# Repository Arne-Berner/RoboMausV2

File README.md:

# Goal
- build a micromouse (from here on out called "rat") from scratch

# Motivation
## The fear of the unknown
I have been working with electronics for a while now, but I never really got into PCB design. I always thought it was too complicated and I would never be able to do it. But I also always wanted to build a micromouse. So I thought, why not combine the two and learn something new in the process.

That being said I also wanted to use my 3D printer more and get rid of that fear that accompanies anything new. Doing this project I feel like I will be able to create electronic devices much more easily in the future. Not only because I learned some tricks on my way, but because I simply have done it before.

## Beginner to Intermediate Rust Project
Let's be honest, coding for embedded systems sound hard. Rust also sounds hard. But weirdly enough, those two things combined are much easier than I thought! I want to provide all the code I used for this project for anyone interested. If you feel like creating electronic devices could be fun, give it a try! Especially the esp32 and rust go really well together. You can [try out Rust on the ESP32 on Wokwi](https://wokwi.com/).

# Parts with their Voltage and Reason I used them

## Placed
### ESP32-s3-mini: 3.3V 
The reason I chose the s3-mini was because it wasn't much more expensive and I was not sure how much processing power will be needed for the project. If I had more time I probably would have chosen an esp32 from the c series. You don't need to use an esp32 at all for a micromouse, but I will need to send the map created by my SLAM-algorithm to my computer via wifi. The STM32 is the MCU that is used for most micromouse.

### USB-C: 5V output
Micro USB tend to break of more easily from PCBs and USB-C has the possibility of using more Volt in later designs, without changing too much.

### AMS1117-3.3: LDO that converts to 3.3V
This seems to be a very common LDO and even though the esp32 is somewhat capable of handling higher voltage than described in the datasheet, I didn't want my project to go up in flames at a bad time.

### L293D (better known as an H-Bridge)
This will let me use my 3.3V from the esp and my 8V from the LiPos to drive my motors. It usually takes one source that ranges from 5V to 36V and another source that will only take 5V. I will see how it works in the project. I could've used an smt h-bridge to minimize the size on the pcb, but running the h-bridge in the wrong manner can destroy it. If that happens (and it will happen) I would like to be able to replace it fast.

### TCS34725 (Color sensor): 2.7V - 3.6V / nom: 3V
I will need to detect the colors of certain places in the labyrinth as an extra task. This seems to be a common and cheap color sensor. It also has a rust library. 

### GY-521 or MPU-6050 (gyroscope sensor): 2.375V - 3.46V
This will help me position orientate my rat. I'm not sure yet, how I will combine this with the input I get from the encoder and what will be used primarily if there is a difference between the two. The mpu-6050 seems to be cheaper but has better specs.

## Not Placed
### SK6812MINI-B-012 (NeoPixel): 5V
This could be used for debugging purposes (and it looks cool), but it needs 5V and that would've drained the LiPos faster than I wanted them to. There is a 3V alternative to the 5V neopixel, but I could not find it on lcsc.

### AMS1117-5.0: LDO that converts to 5V
This would have been necessary if I used the Neopixel above or if the ams1117-3.3 would not be able to handle the lipo voltage.

# Learnings
## How to read a Datasheet instead of "read the datasheet"
When you start in electronics you hear "read the datasheet" a lot. It sounds like bad advice at first, because you probably are asking experienced people about very specific device and datasheets can be hundreds of pages long. Where to start reading up on it? What if there is a feature that you didn't know the name of? Most people rather stop than to "read the datasheet" without knowing where to look for the most important info. 

Later on it feels like "read the datasheet" really was the solution to most problems. But only seemingly so. Experts don't read the full datasheet, even if it is only a few pages long. They won't look at all the data. But they know how to skim the datasheet for the most important info and see if anything is readworthy. But I am no expert and I still need to find answers to my questions. So how to read a datasheet?

There are some basic informations that you most likely want to take a look at:
- volt and ampere (often found as VCC or Vin/Vout info)
- the pinout
- provided example schematics
- (footprints)
With those infos you will have most infos so that your ICs don't burst into flames. It also has the benefit, that most often when looking for those informations you will find other important or odd info that will help you with your project. Be aware that datasheets sometimes contain the data for many variations of IC.

## Copilot and co.
Reading the datasheet might be hard if it is in chinese or if it is hundreds of pages long. Using any LLM to get the gist of it or some pointers where to look for can be very helpfull. But be warned: Especially in electronics halucinations seem to occur very often. They should only be used, if you check the data afterwards. The pinout is very often wrong, the current and voltage vary from the real parts and you can't use it for example schematics. But it will give you words to look for in the datasheet that might be important. 

"What should I be aware of with part XY" or "What could go wrong with wiring X to Y" are the most helpfull prompts.

## Kicad
### Schematics
I like to start with everything at once and see everything come together at the end. But who would have thought that this is neither good in programming, nor in electronics? 

The next project I would definitely draw the schematics for only one or two parts and then check if everything is alright. Do some adjustments, check if everything is alright, put it in the pcb. Rinse and repeat. That way I wouldn't have had to redo big portions of the project and I would have been way faster. Not only that, but I would have some starting point when placing the footprints on the pcb.

Another trick I learned from a friend of mine named "MAG" is to take really good care of a global library and push it to github or any cloud provider. That way you can use it on any machine available to you and using github you could help other people by taking care of that library.

### Libraries and imports
Since I knew I wanted to get the pcb on jlcpcb I mainly used [this website](https://dougy83.github.io/jlcparts/#/) to find the right part. This is a fork of [this repository](https://github.com/yaqwsx/jlcparts) and should be part of that repository soon. It often makes sense to focus on one shop for electronic parts, since shipping and handling fees will stack up fast with different shops. I used [Easyeda cli Plugin](https://github.com/uPesy/easyeda2kicad.py) to get the libraries from EasyEda, since I figured they would fit the parts used by jlc the best.
If I were to start again I would probably use [this Import Plugin](https://github.com/Steffen-W/Import-LIB-KiCad-Plugin#use-of-the-application) instead or go the hard route and learn to draw my own footprints and symbols. Most people that have been doing this for a while seem to prefer using their own footprints. That way there will be no suprises when buying the pcb.

It's also worth mentioning, that adding test points to any power io seems like a good idea. Using test points in general for critical conditions can help tremendously. But what are critical areas? It depends on your project, but when something does not work, the first thing you check is probably the power supplies.

Lastly I have to admit that in most cases you do not need libraries or imports in a project, because kicads default library is very big. But the terms you might be looking for is not the term you are looking for. 

### Symbols
- Symbols are not the parts themselves, but a representation for them
- Symbols most often don't use the right pin attributes, but "unspecified", which results in a lot of errors when using easyeda2kicad
- GND and VCC are all "Power Input"
- Signals that could go in both ways are bidirectional
- Signals that go only in one way are input or output (which you won't find often and could make your life harder)
- a lot of warnings can be mitigated by using "passive" for pins, unless you know they are generating/receiving signals

### Footprints
- Footprints are the actual parts you would probably find. This abstraction between symbols and footprints confused me at first
- drawing them yourself can be a good practice, but the online libraries are much easier to use
- there is always a section about that on every datasheet
- most footprints are saved by their "package", so do not look for the specific ic in kicad, but for the packaging

### PCB
- One layer for horizontal signals and one layer for vertical signals
- Use more space first and then take away as much space as you need
- Draw a trace to see all the connected parts highlighted (this is good, when trying to find connected parts)
- there is a button to delete the whole trace (delete full track)
- there is a button to place a via on the current trace and change layer (place through via)
- put GND vias as close to the pad as possible and with a big trace to lower inductance
- you can use space to get some relative measurements. The origin of one of you coordinate systems in the bottom corner will change

### Planning and Assembly
Using an interactive BOM can be very usefull for any step, but especially the assembly can be structured that way. Checking if your parts are the way they should be, can be done with an interactive html. You can load it on your phone, you can export it for your other projects and you don't need to rewrite anything you don't need. I use the interactive BOM plugin for kicad.

For the actual assembly service on jlcpcb I use a plugin called "Fabrication Toolkit" which you can find in the plugin and content manager in kicad.

### Using Stencils
It can be usefull to place NPTH - holes that do not have any plating around them - to place the stencil properly. You can then use little pegs through both pcb and stencil to place the stencil very fast and accurately.

### Annoying things you want to know before they happen
- if you edit your symbols via schematics, they will only be updated for that one symbol in the schematics. There is no way to save that edit to your actual symbol in the library.
- if you have another window (e.g. the plugin window in the main menu) you cannot click anything in any other kicad window
- interactive bom gets cached, so you need to use ikognito mode
- interactive bom uses the generated bom fields for its fields. Those are only shown, if you updated the schematics editor and imported the changes into the pcb editor

Lastly I would advice you not to use the update pcb with relink too much, if you just used "annotate schematics". This will swap around parts and it's not fun.

## be a copycat
- you don't know what parts you need at the beginning. Just write "gyroscope pcb" on your prefered search or youtube to get a good idea, what might be usefull.

## PCB-Design
### 2 layer PCB vs 4 layer PCB
Truth being told, I have seen very different opinions on this. Some say 4 layers can get much more expensive. This is not necessarily the case when you only use through hole vias, but they are undeniably more expensive. But four layers are also a lot easier to design and depending on who you ask will make the signals less prone to EMI. 

As a rule of thumb I would say starting with a 2 layer pcb is the way to go and then go up to 4 layers, if you need to. For example when you have different voltages on your board that cannot easily be separate. But there is not much lost when you go for 4 layers from the beginning. Depending on how you click on what option in jlcpcb the price for this 4 layer board was 5$ more instead of the same size with 2 layers.

### Energie takes the path of least impedance, not resistance
Which makes a big difference in an AC Environment. But most hobby projects are DC, so why bother? Since any pulsed DC signal counts as a AC signal. This means for you, that you will have to keep the distance between the signal, ground and vcc very close to each other. This can be done via a good PCB layer stackup and thoughtfull routing.

### Signals will influence each other
Any Signal will be able to influence any other Signal next to it. Even though signals might look more tidies up, when you use the minimum distance possible by your PCB manufacturer, you should try to widen the gap between them. There is a tradeoff here, where some signals need to be coupled and some signals need to travel the shortest path possible.

### Important rules (that can be broken, if you know what you are doing) ... which I don't
- keep signals spaced as wide as possible
- short distance between forward and back pass
- keep GND and VCC via close to each other
- antennas work best with nothing in the way (place it at the edge)
- 3.3V signals should only reference 3.3V power in the current or next layer
- separate analog and digital signals spatially
- keep the distance between analog and digital 20x as wide as between ground and signal plane (no need to split the ground plane)
- different voltages get different areas on the board (the planes can be split if no other signals are crossing those areas)
- different frequencies get different areas on the board
- use ground vias to get signals from one layer to another
- don't put power and ground on layer 2 and 3 on a 4 layer board, because of the bigger distance
- on a 6 layer board don't put them on 2 and 5
- power layers should be near high-speed ICs
- use test pads
- PCB layers are stacked in pairs (distance wise)

# Resources
## Micromouse
There are some places to look at, but the best resource by far that I could find was [Micromouse Project from UCLA](https://projects.ieeebruins.com/micromouse/).

## PCB and KiCad
A video about proper grounding on pcb can be found [here](https://www.youtube.com/watch?v=ySuUZEjARPY&t=7540s&pp=ygURcGNiIGdyb3VuZCBwbGFuZSA%3D). [Robert Feranec](https://www.youtube.com/@RobertFeranec) also has very nice tutorials on different topics, even though they can be quite wordy. When it comes to nice and concise material I like [Phil's Lab](https://www.youtube.com/@PhilsLab). The audio is good, there are some good examples and he only concentrates on the most important points. Also the [getting started docs from KiCad](https://docs.kicad.org/8.0/en/getting_started_in_kicad/getting_started_in_kicad.html) are easy to read. Please let me know if you know any "non-youtube" sources that are well written!

## Rust
I have to admit, that after working through some nice [beginner std tutorials](https://docs.esp-rs.org/std-training/) (there is also [a no-std version](https://docs.esp-rs.org/no_std-training/)) which you can use with [Wokwi - an online esp32 simulator](https://wokwi.com/), I mostly look at the [esp-rs repos](https://github.com/esp-rs) and their respective examples. That is not the case because I am a hardcore "read the docs N00b" kinda person, but because the examples there and their docs are very well written and always up-to-date! 

But let's be serious, there always is a point, where you run into a wall with the docs, because you just don't know some technique that exists. The best place to find help then is [the esp matrix room](https://matrix.to/#/#esp-rs:matrix.org). There are a ton of helpfull people that will even answer the most basic questions in a respectful way. 

I think there should be an honorable mention for the [embedded rustaceans blog](https://blog.theembeddedrustacean.com/) which can help you at the beginning a lot and [awesome esp rust](https://github.com/esp-rs/awesome-esp-rust) which can be an inspiration for cool projects or topics you didn't know about.

# Next Versions
## learnings for V1
- [x] the holes for the case should be 3mm and those for the motors the small size
- [x] add pinheader for jtag
- [ ] add markings for + and - in the relevant places
- [x] gyroscope needs more space, to be able to be used in the middle
- [x] use jst-ph instead of xh
- [x] go up one size for smd. There is no benefit in 0403 when I solder it myself
- [x] use a stencil next time, when working with usb-c and Quad Flat No-Lead chips
- [ ] build cases for all the sensors/pcbs used
- [x] I don't need to care too much about interference from the motors for the usb since they will be turned off while flashing.
- [x] I want the testpoints near the peripheral they are for, because it's easier to test and see what is going on
- [ ] better naming and silkscreen helps a lot

## For Version 2
- [ ] make the LiPos chargeable
- [ ] use STM32 for the IR Sensors/ADC because they are less noisy
- [x] add proper silkscreen
I did think about adding lipo chargers, but:
1. It takes up some space to do that
2. It's hard to charge Lipos from one source in parallel
3. There are some nice TC4056 breakout boards which I can use, while running tests on the mouse

I did not use the STM32 for IR Sensors/ADC yet, because the quality of the IR sensor was somewhat sufficient and I needed to move fast, after Version 1 did not work at all.

## For Version 3
- [ ] connect ground to ground of the battery...
- [ ] use STM32 for the IR Sensors/ADC because they are less noisy
- [ ] get NPTH points for better alignment with the stencil
- [ ] go down to 2 layers so that it is cheaper to replicate

## What went wrong
I misunderstood "different voltages get different areas on the board (the planes can be split if no other signals are crossing those areas)". It means that you should split the power planes, if you have different voltages on your board. I thought it meant that you should split the ground planes beneath the power planes. There is no need for that, since in high frequency areas the signal will travel above the corresponding ground anyway. If it was closer to DC voltage, then it would just travel the shortes path through ground.

I definitely shouldn't have used a trackpad. My wrists hurt really bad and it was much slower than it needed to be.

I assumed that the adc multiplexing works across _all_ pins, but it only works for the first 14 or so. Testing every pin as I would like to use them on the board would have helped a lot!

## What went right
I could achieve a very small mouse with 4 layers. I'm not sure if I was able to do so with less layers.

I got over the fear of doing something for the first time and I learned a lot about electronics.

# Thanks
Hannes and Mohamad have helped me tremendously. Robert gave me some ideas for the next version and what I could have done better this time. Thank you!

# JLCPCB pricing
This has been really confusing to me, so that is why I am adding this section here. 
If you want to get your pcb from jlc pcb there are some weird things you have to look out for. For example, if you add a pcb with 4 layers from the beginning, it will have a lower price, than if you had added a 2 layer pcb and then changed it to a 4 layer pcb. The same goes for the size of the pcb. If you add a pcb with 100x100mm and then change it to 100x150mm it will be more expensive than if you had added a 100x150mm pcb from the beginning. 

Not only that, it gets really niche if you look at the assembly service. There are "basic", and "extended" parts. At least it looks like that. There are also "preferred extended" parts, which act like basic parts, if you use the "economic assembly". But first things first:
The assembly costs depending on what parts you choose. If you choose only basic parts and no special pcb, then this will get categorized as "economic assembly". That is the cheapest option you can get.

If you add "preferred extended" parts to this, it should stay in the "economic assembly" category. But if you add "extended" parts to this, it will get categorized as "standard assembly". This not only is the most expensive option, but you also have to pay 3$ for every _different_ extended part. So if you have some special transistor a thousand times on your board, that is 3$ extra for you. But if you have 10 different extended parts on your board, that is 30$ extra for you. This extra price comes from the fact, that they have to place those extended parts per hand into the machines, because they don't have the big reels for the most used parts.

Lastly there is a shipping option called "global direct standard line" which is much cheaper than the other options. 

## Some inaccurate information about the prices
- 2 layer 100x100mm: around 5$
- 4 layer 100x100mm: around 10$
- 4 layer bigger sizes: around 35 dollar$
- assembly economic: 7-10 dollar
- assembly standard: 20-30 dollar
- any extended part: 3 dollar
- global direct standard line: 2-5 dollar
- stencil: extra 2-20 dollar (mostly because of the shipping costs)

Overall I would say that small projects that don't need more than 2 layers should be done as such. Although 4 layers can give you a lot better signals and smaller boards, so I would always go for a 4 layer board that's smaller than 100x100 over a bigger 2 layer board.
The assembly is quite cheap, if you don't like soldering and would pay yourself for that time. The only problem is, that they don't have all the parts you might need and as soon as you use extended parts, it'll get really expensive really fast.

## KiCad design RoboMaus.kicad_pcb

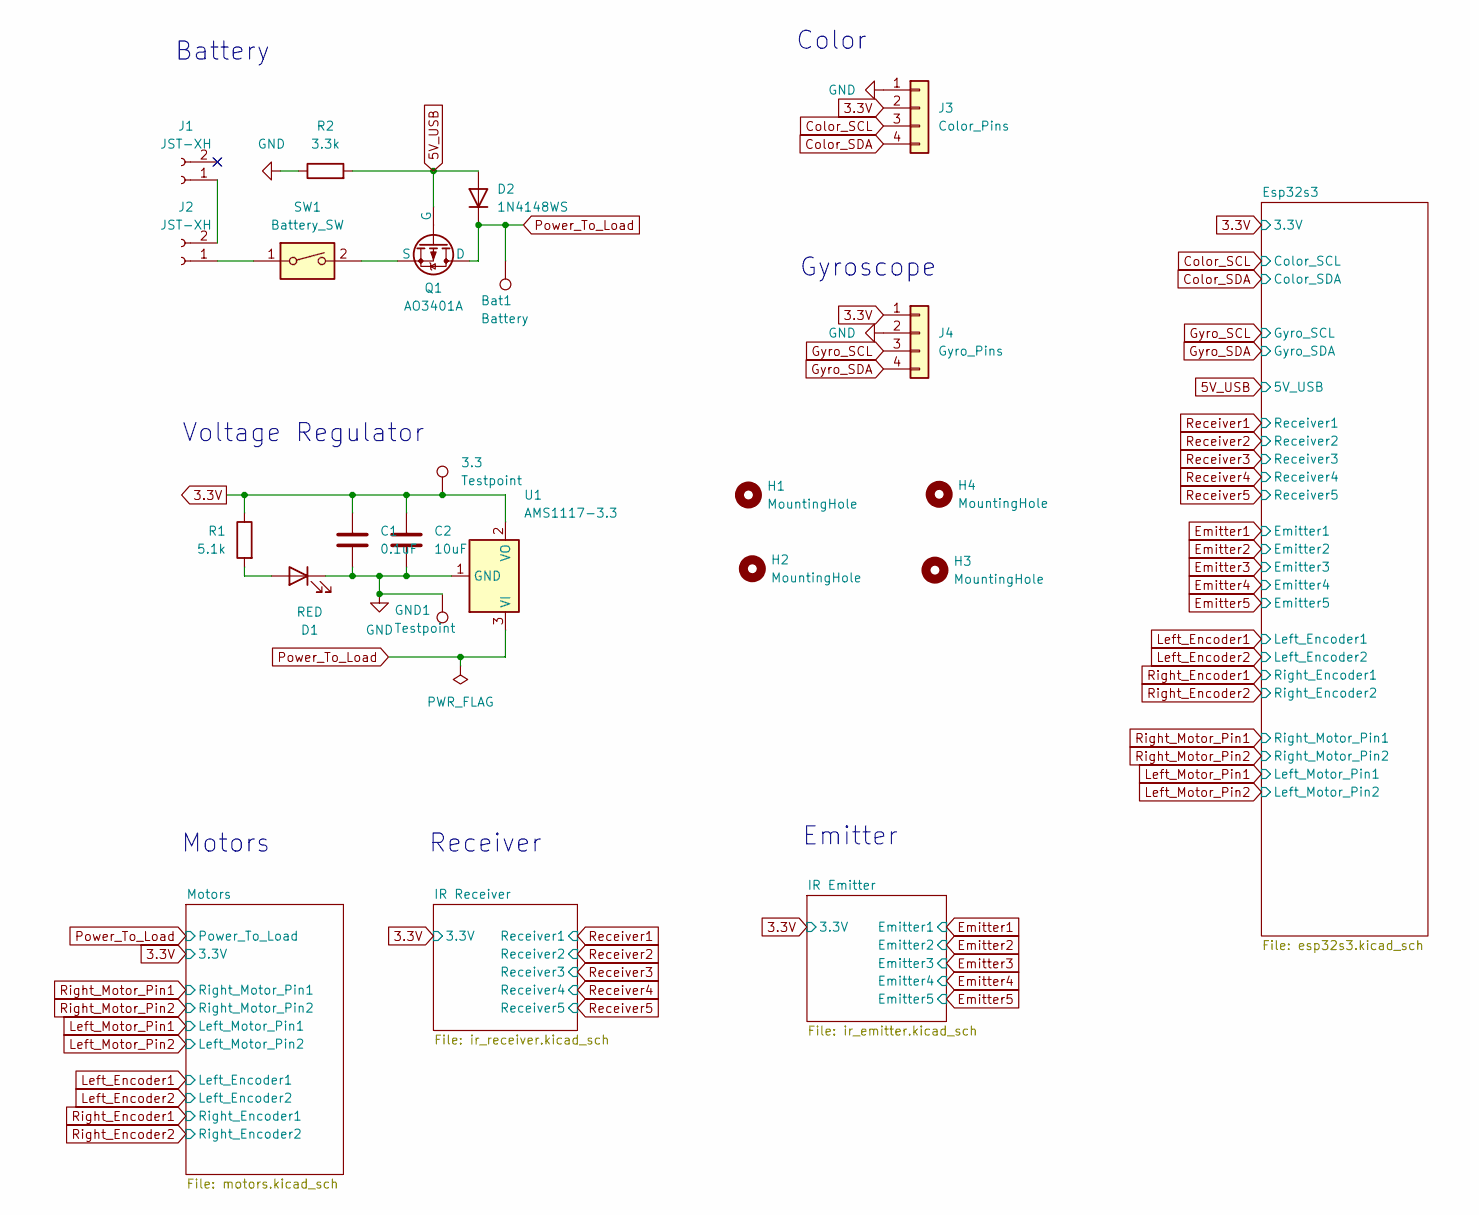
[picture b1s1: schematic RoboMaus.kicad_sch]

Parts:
3.3: Testpoint; TestPoint_THTPad_2.0x2.0mm_Drill1.0mm
Bat1: Battery; TestPoint_THTPad_2.0x2.0mm_Drill1.0mm
C1: 0.1uF; C_0805_2012Metric_Pad1.18x1.45mm_HandSolder
C2: 10uF; C_0805_2012Metric_Pad1.18x1.45mm_HandSolder
D1: RED; LED_0603_1608Metric_Pad1.05x0.95mm_HandSolder
D2: 1N4148WS; D_SOD-323; MPN 1N4148WS; JLCBasic basic
GND1: Testpoint; TestPoint_THTPad_2.0x2.0mm_Drill1.0mm
H1, H2, H3, H4: MountingHole; MountingHole_3.2mm_M3_DIN965_Pad
J1, J2: JST-XH; JST_XH_B2B-XH-A_1x02_P2.50mm_Vertical
J3: Color_Pins; PinHeader_1x04_P2.54mm_Vertical
J4: Gyro_Pins; PinHeader_1x04_P2.54mm_Vertical
Q1: AO3401A; SOT-23
R1: 5.1k; R_0603_1608Metric_Pad0.98x0.95mm_HandSolder; MPN 0603WAF5101T5E; JLCBasic basic
R2: 3.3k; R_0603_1608Metric_Pad0.98x0.95mm_HandSolder; MPN 0603WAF3301T5E; JLCBasic basic
SW1: Battery_SW; SW_DIP_SPSTx01_Slide_9.78x4.72mm_W7.62mm_P2.54mm
U1: AMS1117-3.3; SOT-223-3_TabPin2

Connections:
3.3V: 3.3.1, C1.1, C2.1, J3.2, J4.1, R1.1, U1.2 (VO); also elsewhere on the board
5V_USB: D2.2 (A), Q1.2 (G), R2.2; also elsewhere on the board
Color_SCL: J3.3; also elsewhere on the board
Color_SDA: J3.4; also elsewhere on the board
GND: C1.2, C2.2, D1.1 (K), GND1.1, J3.1, J4.2, R2.1, U1.1 (GND); also elsewhere on the board
Gyro_SCL: J4.3; also elsewhere on the board
Gyro_SDA: J4.4; also elsewhere on the board
unnamed: D1.2 (A), R1.2
unnamed: J1.1, J2.2
unnamed: J2.1, SW1.1
unnamed: Q1.3 (S), SW1.2
Power_To_Load: Bat1.1, D2.1 (K), Q1.1 (D), U1.3 (VI); also elsewhere on the board

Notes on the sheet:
Voltage Regulator
Battery
Emitter
Motors
Receiver
Gyroscope
Color

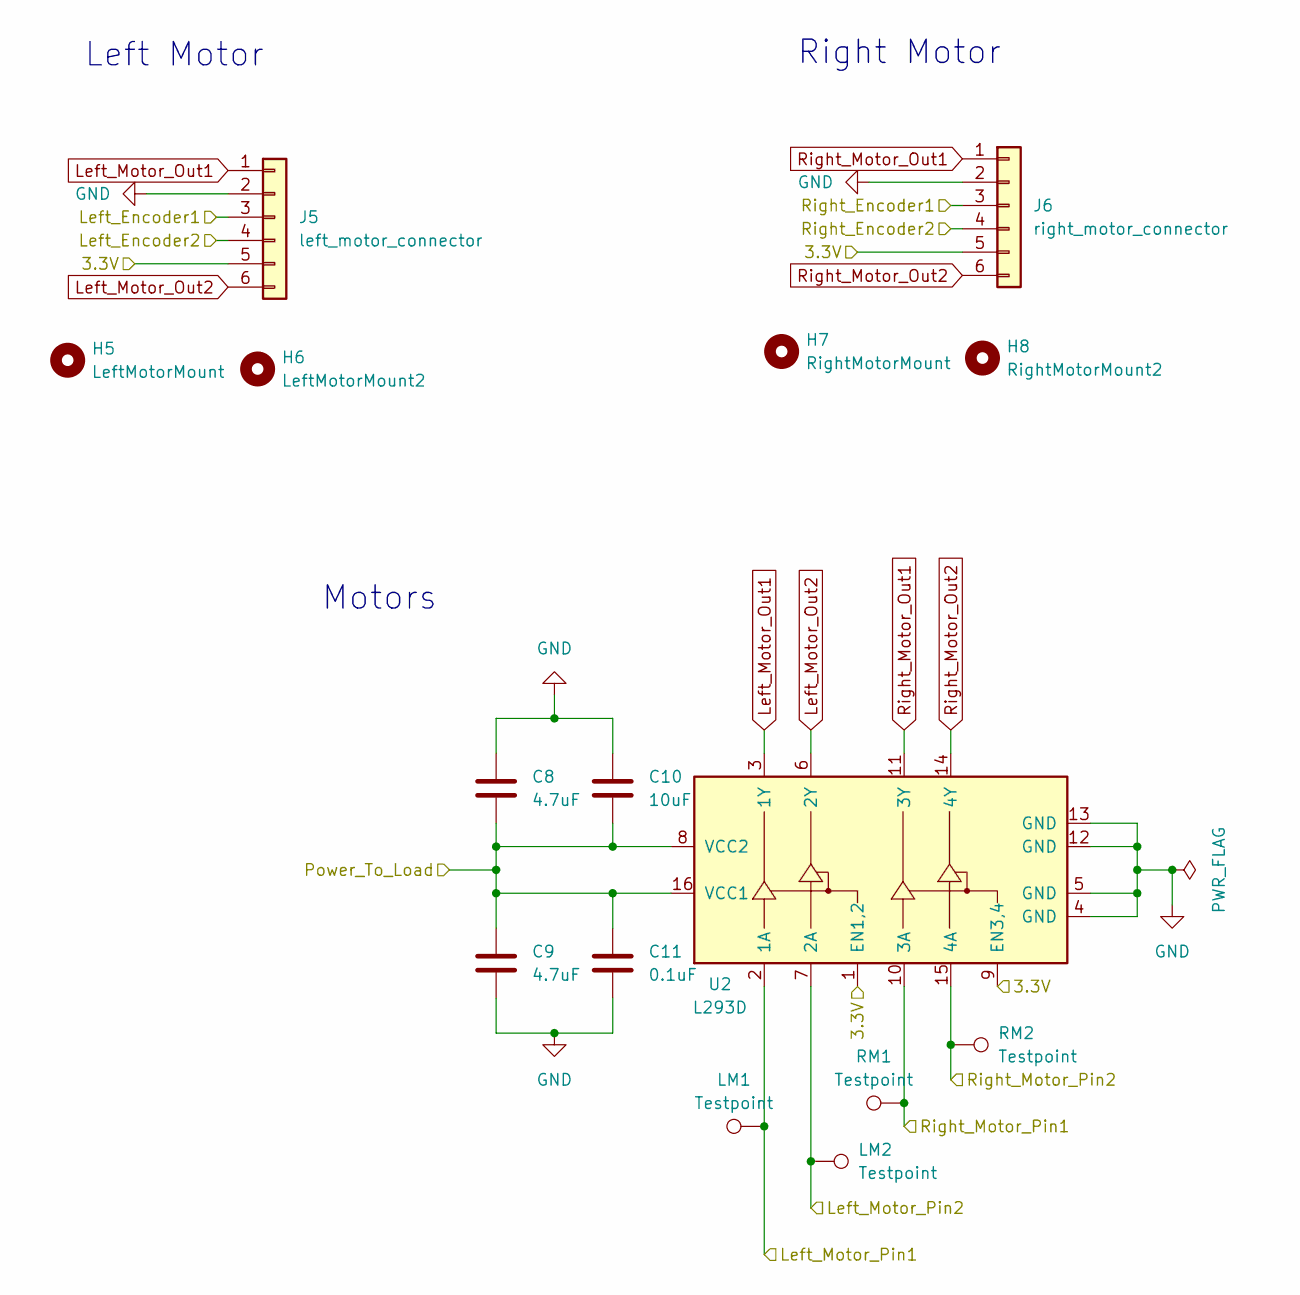
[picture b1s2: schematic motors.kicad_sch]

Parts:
C8, C9: 4.7uF; C_0805_2012Metric_Pad1.18x1.45mm_HandSolder
C10: 10uF; C_0805_2012Metric_Pad1.18x1.45mm_HandSolder
C11: 0.1uF; C_0805_2012Metric_Pad1.18x1.45mm_HandSolder
H5: LeftMotorMount; MountingHole_2.2mm_M2_DIN965_Pad
H6: LeftMotorMount2; MountingHole_2.2mm_M2_DIN965_Pad
H7: RightMotorMount; MountingHole_2.2mm_M2_DIN965_Pad
H8: RightMotorMount2; MountingHole_2.2mm_M2_DIN965_Pad
J5: left_motor_connector; JST_XH_B6B-XH-A_1x06_P2.50mm_Vertical
J6: right_motor_connector; JST_XH_B6B-XH-A_1x06_P2.50mm_Vertical
LM1, LM2: Testpoint; TestPoint_THTPad_2.0x2.0mm_Drill1.0mm
RM1, RM2: Testpoint; TestPoint_THTPad_2.0x2.0mm_Drill1.0mm
U2: L293D; DIP-16_W7.62mm

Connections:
3.3V: J5.5, J6.5, U2.1 (EN1,2), U2.9 (EN3,4); also elsewhere on the board
GND: C8.2, C9.2, C10.2, C11.2, J5.2, J6.2, U2.4 (GND), U2.5 (GND), U2.12 (GND), U2.13 (GND); also elsewhere on the board
Left_Encoder1: J5.3; also elsewhere on the board
Left_Encoder2: J5.4; also elsewhere on the board
Left_Motor_Out1: J5.1, U2.3 (1Y)
Left_Motor_Out2: J5.6, U2.6 (2Y)
Left_Motor_Pin1: LM1.1, U2.2 (1A); also elsewhere on the board
Left_Motor_Pin2: LM2.1, U2.7 (2A); also elsewhere on the board
Power_To_Load: C8.1, C9.1, C10.1, C11.1, U2.8 (VCC2), U2.16 (VCC1); also elsewhere on the board
Right_Encoder1: J6.3; also elsewhere on the board
Right_Encoder2: J6.4; also elsewhere on the board
Right_Motor_Out1: J6.1, U2.11 (3Y)
Right_Motor_Out2: J6.6, U2.14 (4Y)
Right_Motor_Pin1: RM1.1, U2.10 (3A); also elsewhere on the board
Right_Motor_Pin2: RM2.1, U2.15 (4A); also elsewhere on the board

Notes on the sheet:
Left Motor
Motors
Right Motor

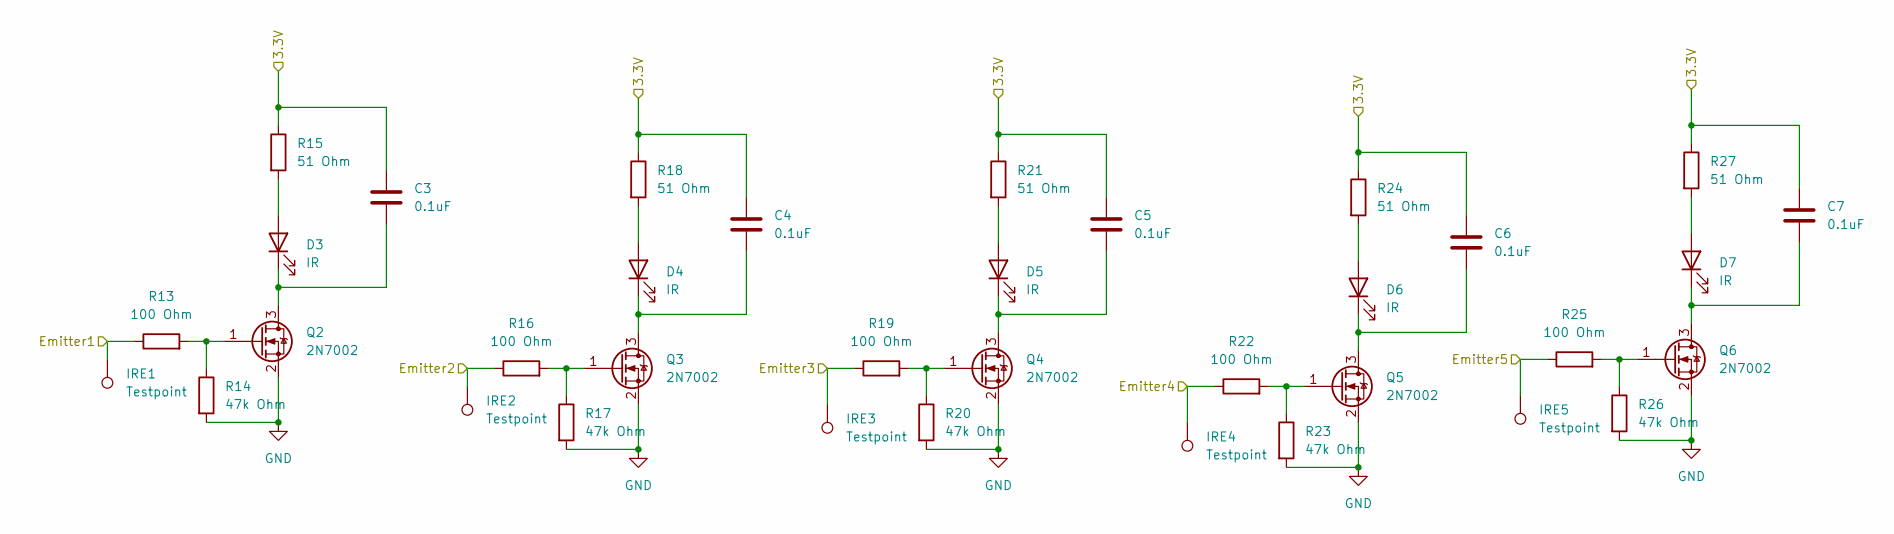
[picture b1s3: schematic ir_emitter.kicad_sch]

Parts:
C3, C4, C5, C6, C7: 0.1uF; C_0805_2012Metric_Pad1.18x1.45mm_HandSolder
D3, D4, D5, D6, D7: IR; LED_D5.0mm_IRGrey
IRE1, IRE2, IRE3, IRE4, IRE5: Testpoint; TestPoint_THTPad_2.0x2.0mm_Drill1.0mm
Q2, Q3, Q4, Q5, Q6: 2N7002; SOT-23
R13, R16, R19, R22, R25: 100 Ohm; R_0603_1608Metric_Pad0.98x0.95mm_HandSolder
R14, R17, R20, R23, R26: 47k Ohm; R_0603_1608Metric_Pad0.98x0.95mm_HandSolder
R15, R18, R21, R24, R27: 51 Ohm; R_0603_1608Metric_Pad0.98x0.95mm_HandSolder

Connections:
3.3V: C3.1, C4.1, C5.1, C6.1, C7.1, R15.1, R18.1, R21.1, R24.1, R27.1; also elsewhere on the board
Emitter1: IRE1.1, R13.1; also elsewhere on the board
Emitter2: IRE2.1, R16.1; also elsewhere on the board
Emitter3: IRE3.1, R19.1; also elsewhere on the board
Emitter4: IRE4.1, R22.1; also elsewhere on the board
Emitter5: IRE5.1, R25.1; also elsewhere on the board
GND: Q2.2 (S), Q3.2 (S), Q4.2 (S), Q5.2 (S), Q6.2 (S), R14.2, R17.2, R20.2, R23.2, R26.2; also elsewhere on the board
unnamed: D3.2 (A), R15.2
unnamed: C3.2, D3.1 (K), Q2.3 (D)
unnamed: D4.2 (A), R18.2
unnamed: C4.2, D4.1 (K), Q3.3 (D)
unnamed: D5.2 (A), R21.2
unnamed: C5.2, D5.1 (K), Q4.3 (D)
unnamed: D6.2 (A), R24.2
unnamed: C6.2, D6.1 (K), Q5.3 (D)
unnamed: D7.2 (A), R27.2
unnamed: C7.2, D7.1 (K), Q6.3 (D)
unnamed: Q2.1 (G), R13.2, R14.1
unnamed: Q3.1 (G), R16.2, R17.1
unnamed: Q4.1 (G), R19.2, R20.1
unnamed: Q5.1 (G), R22.2, R23.1
unnamed: Q6.1 (G), R25.2, R26.1

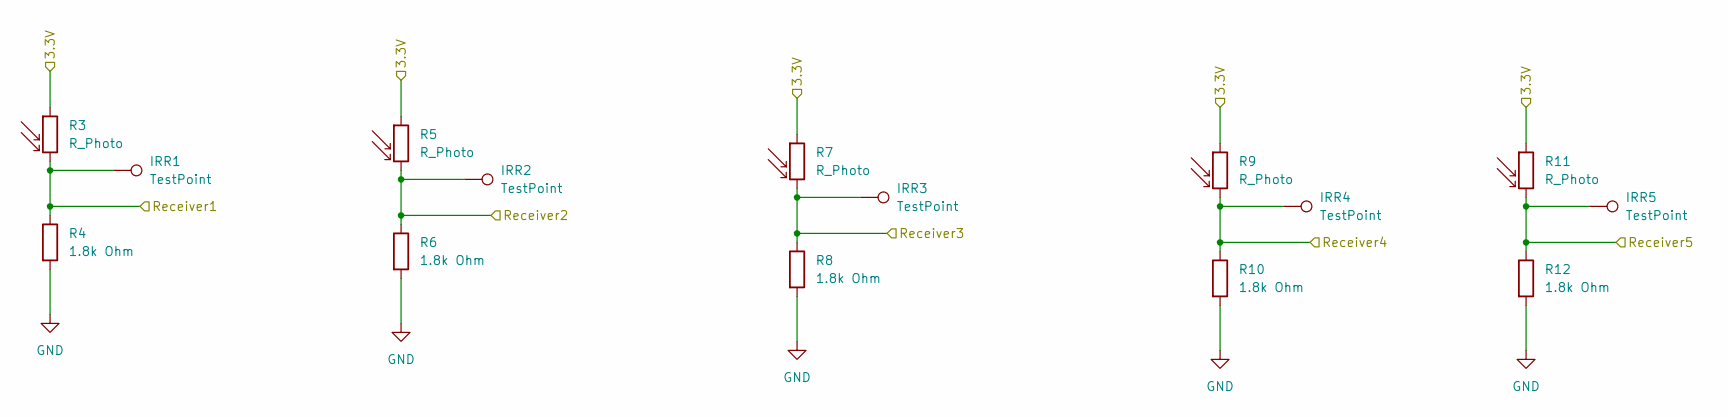
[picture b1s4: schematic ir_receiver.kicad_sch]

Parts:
IRR1, IRR2, IRR3, IRR4, IRR5: TestPoint; TestPoint_THTPad_2.0x2.0mm_Drill1.0mm
R3, R5, R7, R9, R11: R_Photo; LED_D5.0mm_IRBlack
R4, R6, R8, R10, R12: 1.8k Ohm; R_0603_1608Metric_Pad0.98x0.95mm_HandSolder

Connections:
3.3V: R3.1, R5.1, R7.1, R9.1, R11.1; also elsewhere on the board
GND: R4.2, R6.2, R8.2, R10.2, R12.2; also elsewhere on the board
Receiver1: IRR1.1, R3.2, R4.1; also elsewhere on the board
Receiver2: IRR2.1, R5.2, R6.1; also elsewhere on the board
Receiver3: IRR3.1, R7.2, R8.1; also elsewhere on the board
Receiver4: IRR4.1, R9.2, R10.1; also elsewhere on the board
Receiver5: IRR5.1, R11.2, R12.1; also elsewhere on the board

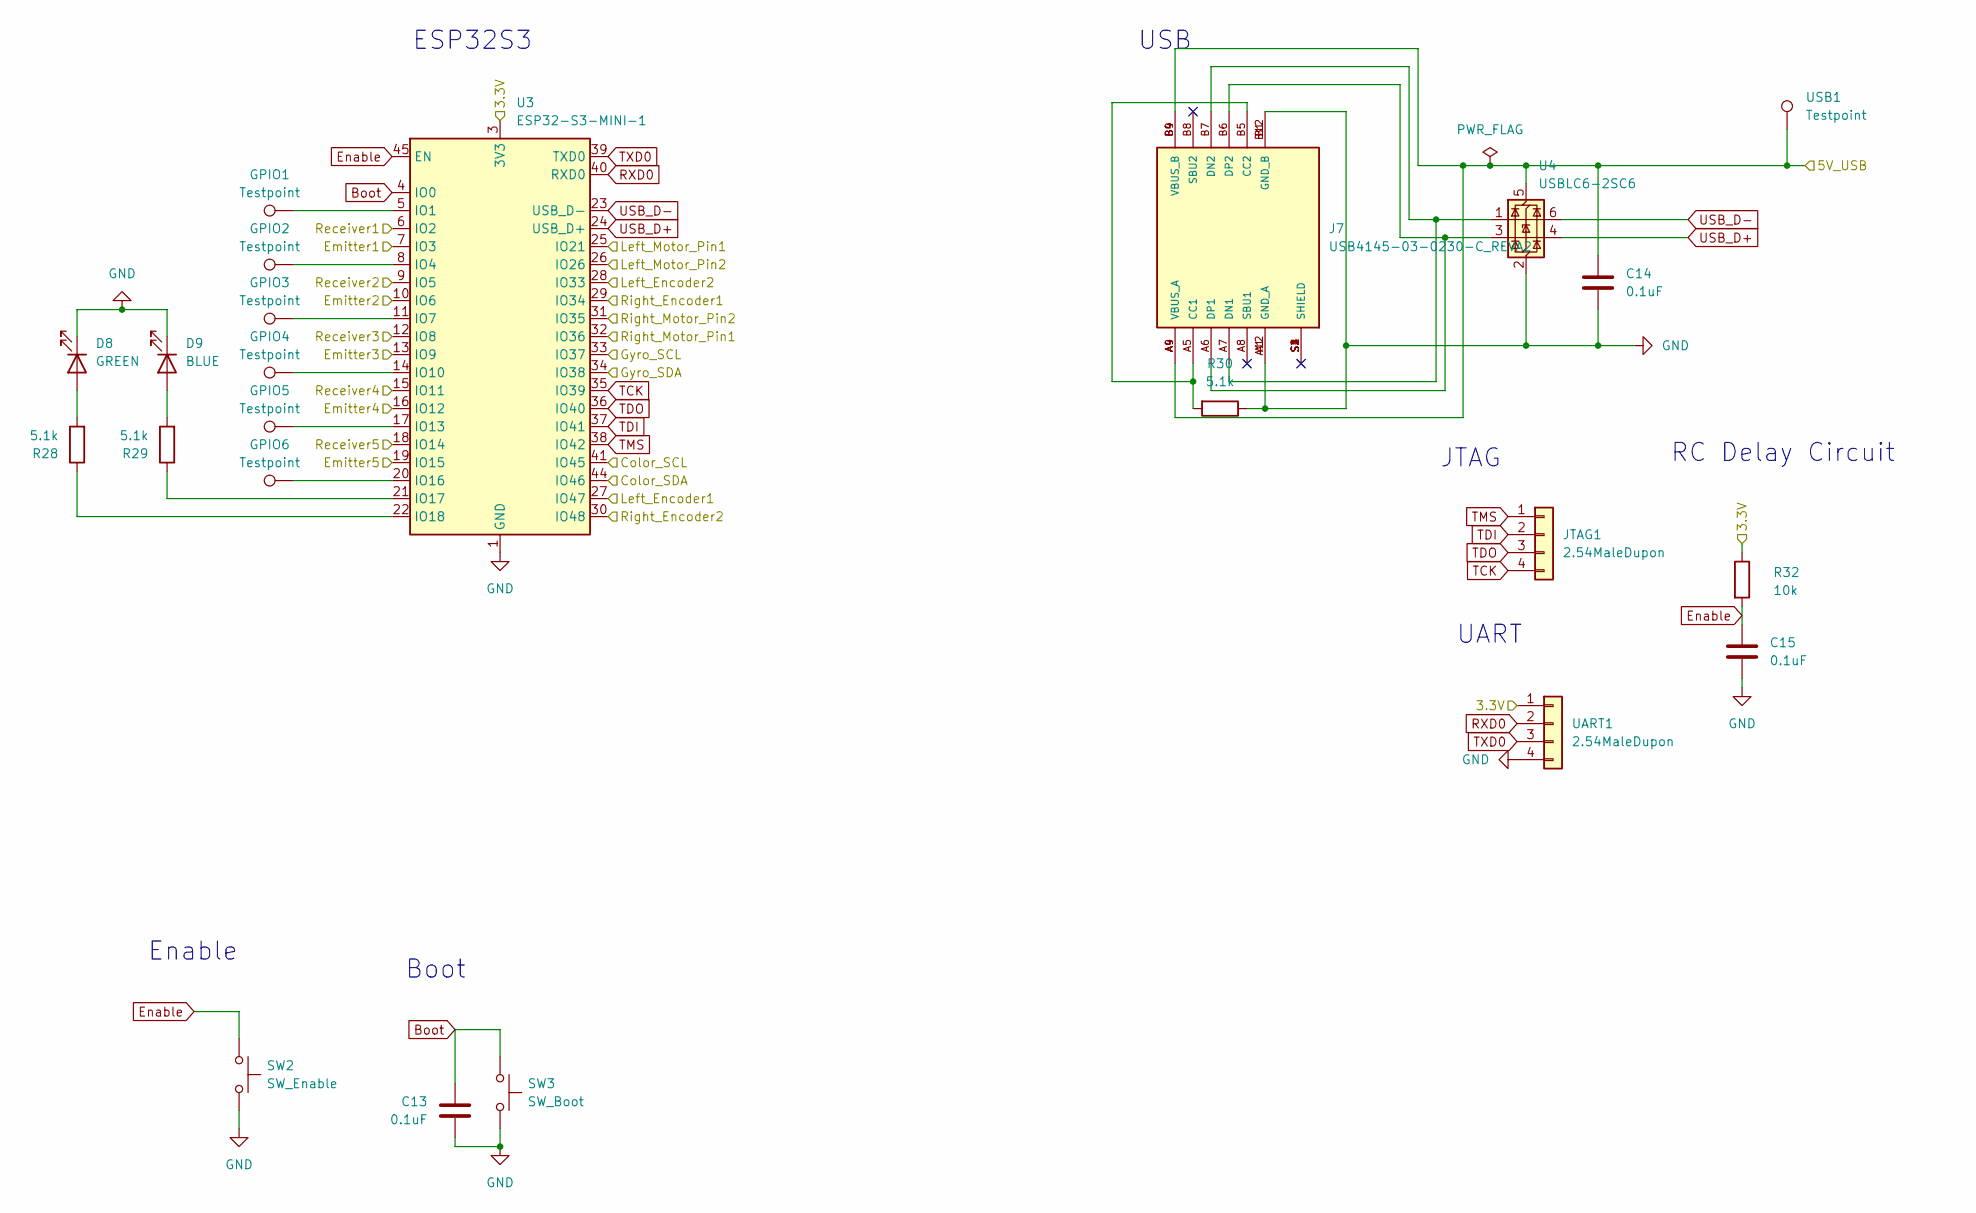
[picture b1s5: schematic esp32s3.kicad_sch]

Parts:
C13, C14, C15: 0.1uF; C_0805_2012Metric_Pad1.18x1.45mm_HandSolder
D8: GREEN; LED_0603_1608Metric_Pad1.05x0.95mm_HandSolder
D9: BLUE; LED_0603_1608Metric_Pad1.05x0.95mm_HandSolder
GPIO1, GPIO2, GPIO3, GPIO4, GPIO5, GPIO6: Testpoint; TestPoint_THTPad_2.0x2.0mm_Drill1.0mm
J7: USB4145-03-0230-C_REVA2; GCT_USB4145-03-0230-C_REVA2; PARTREV A2
JTAG1: 2.54MaleDupon; PinHeader_1x04_P2.54mm_Vertical
R28, R29, R30: 5.1k; R_0603_1608Metric_Pad0.98x0.95mm_HandSolder; MPN 0603WAF5101T5E; JLCBasic basic
R32: 10k; R_0603_1608Metric_Pad0.98x0.95mm_HandSolder; MPN 0603WAF3301T5E; JLCBasic basic
SW2: SW_Enable; SW_Push_1P1T_XKB_TS-1187A
SW3: SW_Boot; SW_Push_1P1T_XKB_TS-1187A
U3: ESP32-S3-MINI-1; ESP32-S2-MINI-1
U4: USBLC6-2SC6; SOT-23-6
UART1: 2.54MaleDupon; PinHeader_1x04_P2.54mm_Vertical
USB1: Testpoint; TestPoint_THTPad_2.0x2.0mm_Drill1.0mm

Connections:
3.3V: R32.1, U3.3 (3V3), UART1.1; also elsewhere on the board
5V_USB: C14.1, J7.A4 (VBUS_A), J7.A9 (VBUS_A), J7.B4 (VBUS_B), J7.B9 (VBUS_B), U4.5 (VBUS), USB1.1; also elsewhere on the board
Boot: C13.1, SW3.1, U3.4 (IO0)
Color_SCL: U3.41 (IO45); also elsewhere on the board
Color_SDA: U3.44 (IO46); also elsewhere on the board
Emitter1: U3.7 (IO3); also elsewhere on the board
Emitter2: U3.10 (IO6); also elsewhere on the board
Emitter3: U3.13 (IO9); also elsewhere on the board
Emitter4: U3.16 (IO12); also elsewhere on the board
Emitter5: U3.19 (IO15); also elsewhere on the board
Enable: C15.1, R32.2, SW2.1, U3.45 (EN)
GND: C13.2, C14.2, C15.2, D8.1 (K), D9.1 (K), J7.A1 (GND_A), J7.A12 (GND_A), J7.B1 (GND_B), J7.B12 (GND_B), R30.1, SW2.2, SW3.2, U3.1 (GND), U3.2 (GND), U3.42 (GND), U3.43 (GND), U3.46 (GND), U3.47 (GND), U3.48 (GND), U3.49 (GND), U3.50 (GND), U3.51 (GND), U3.52 (GND), U3.53 (GND), U3.54 (GND), U3.55 (GND), U3.56 (GND), U3.57 (GND), U3.58 (GND), U3.59 (GND), U3.60 (GND), U3.61 (GND), U3.62 (GND), U3.63 (GND), U3.64 (GND), U3.65 (GND), U4.2 (GND), UART1.4; also elsewhere on the board
Gyro_SCL: U3.33 (IO37); also elsewhere on the board
Gyro_SDA: U3.34 (IO38); also elsewhere on the board
Left_Encoder1: U3.27 (IO47); also elsewhere on the board
Left_Encoder2: U3.28 (IO33); also elsewhere on the board
Left_Motor_Pin1: U3.25 (IO21); also elsewhere on the board
Left_Motor_Pin2: U3.26 (IO26); also elsewhere on the board
unnamed: D8.2 (A), R28.2
unnamed: D9.2 (A), R29.2
unnamed: J7.A5 (CC1), J7.B5 (CC2), R30.2
unnamed: J7.A7 (DN1), J7.B7 (DN2), U4.1 (I/O1)
unnamed: J7.A6 (DP1), J7.B6 (DP2), U4.3 (I/O2)
unnamed: GPIO1.1, U3.5 (IO1)
unnamed: GPIO2.1, U3.8 (IO4)
unnamed: GPIO3.1, U3.11 (IO7)
unnamed: GPIO4.1, U3.14 (IO10)
unnamed: GPIO5.1, U3.17 (IO13)
unnamed: GPIO6.1, U3.20 (IO16)
unnamed: R29.1, U3.21 (IO17)
unnamed: R28.1, U3.22 (IO18)
RXD0: U3.40 (RXD0), UART1.2
Receiver1: U3.6 (IO2); also elsewhere on the board
Receiver2: U3.9 (IO5); also elsewhere on the board
Receiver3: U3.12 (IO8); also elsewhere on the board
Receiver4: U3.15 (IO11); also elsewhere on the board
Receiver5: U3.18 (IO14); also elsewhere on the board
Right_Encoder1: U3.29 (IO34); also elsewhere on the board
Right_Encoder2: U3.30 (IO48); also elsewhere on the board
Right_Motor_Pin1: U3.32 (IO36); also elsewhere on the board
Right_Motor_Pin2: U3.31 (IO35); also elsewhere on the board
TCK: JTAG1.4, U3.35 (IO39)
TDI: JTAG1.2, U3.37 (IO41)
TDO: JTAG1.3, U3.36 (IO40)
TMS: JTAG1.1, U3.38 (IO42)
TXD0: U3.39 (TXD0), UART1.3
USB_D+: U3.24 (USB_D+), U4.4 (I/O2)
USB_D-: U3.23 (USB_D-), U4.6 (I/O1)

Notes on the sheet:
JTAG
Boot
USB
ESP32S3
RC Delay Circuit
UART
Enable

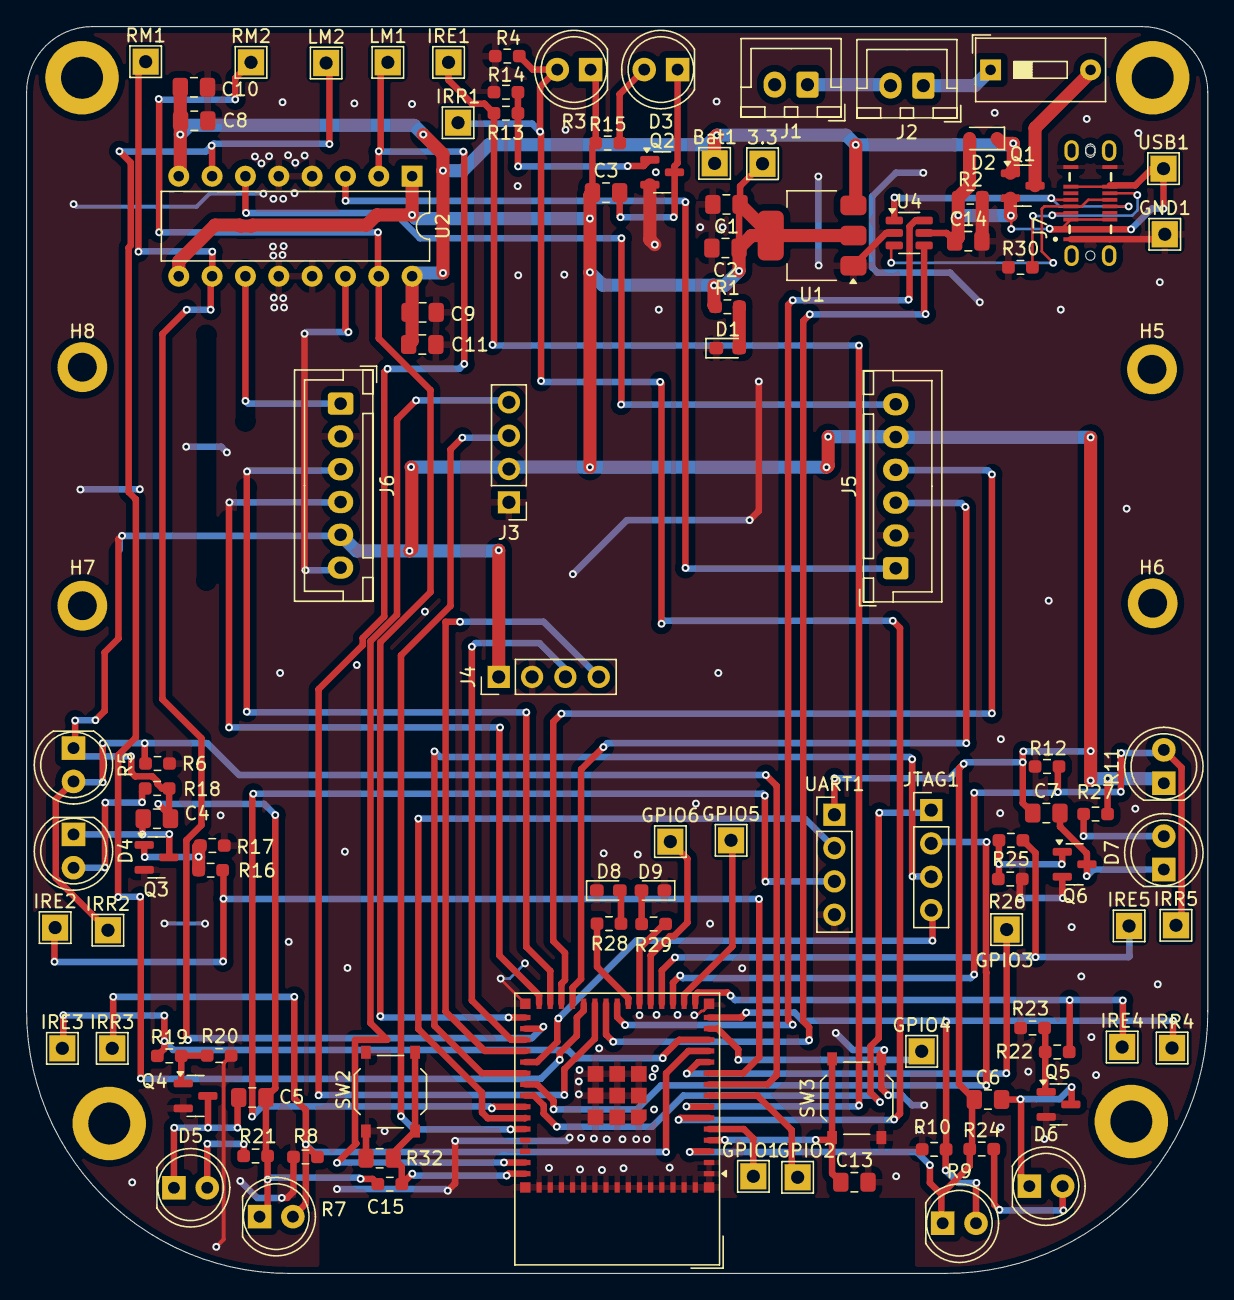
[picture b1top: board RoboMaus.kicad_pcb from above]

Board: 4 copper layers, 90.0 x 95.0 mm, 108 parts (0 on the bottom side), 72 nets.

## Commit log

2025-01-03 feat:initial commit
2025-01-03 schematic: all errors and warnings gone
2025-01-04 pcb: all wired up, most warnings can't be fixed.
2025-01-04 pcb: fixed the wrong mounting holes...
2025-01-07 docs: some notes about getting the stencil right
2025-01-07 docs: updated the old docs
2025-01-07 docs: updated some mistakes and learnings from v1
2025-01-07 docs: kicad uses packaging not ics
2025-01-07 docs: kicad uses packaging not ics.. the right way
2025-01-16 docs: I forgot to connect the battery ground
